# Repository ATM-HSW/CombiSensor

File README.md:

# CombiSensor
MCU plattform + Sensor module for several environmental sensors + LoRaWAN

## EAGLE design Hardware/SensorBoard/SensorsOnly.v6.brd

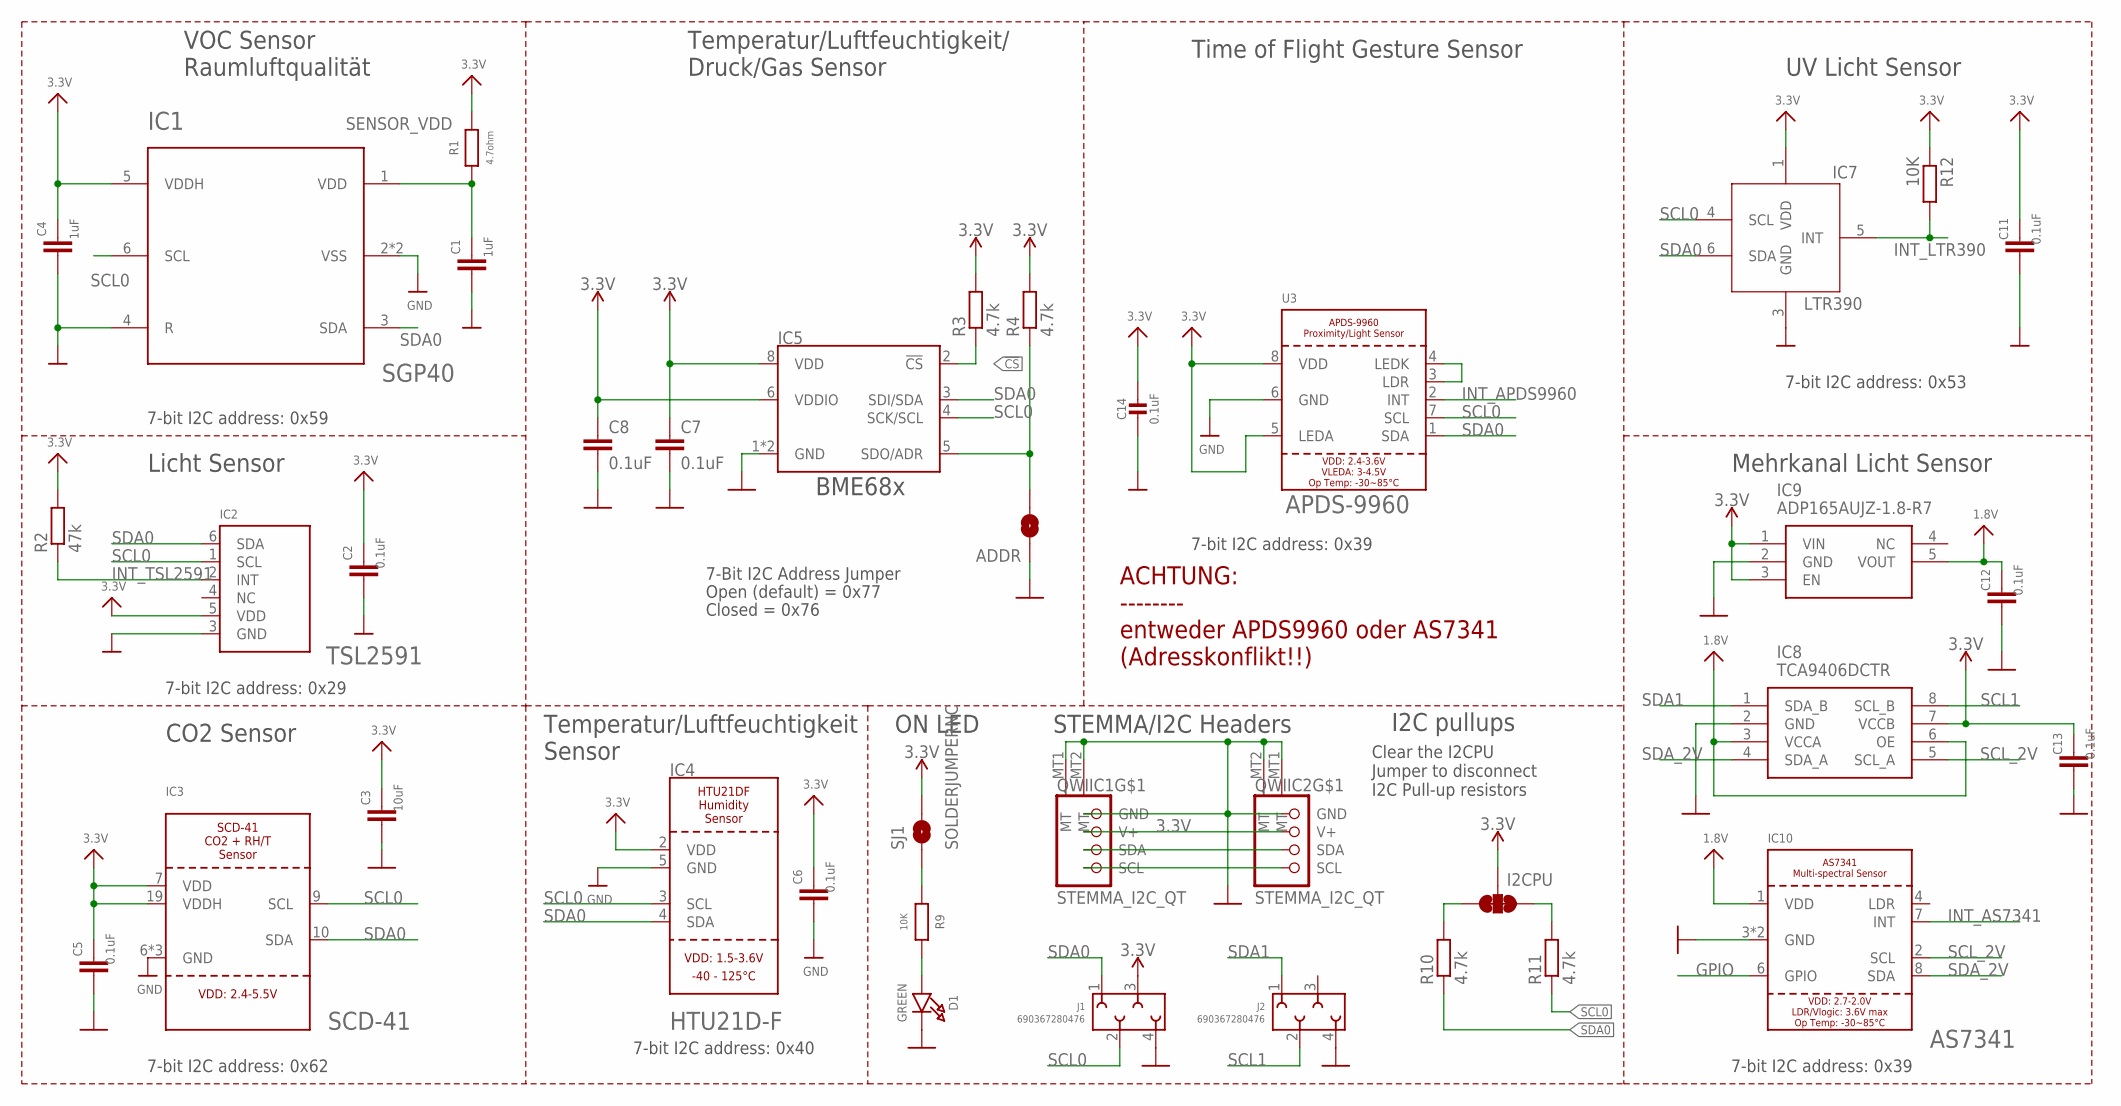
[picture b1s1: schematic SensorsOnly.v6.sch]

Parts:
ADDR: JUMPER-SMT_2_NO_SILK; SMT-JUMPER_2_NO_SILK
C1, C4: 1uF; C0805
C2, C5, C6, C7, C8, C11, C12, C13: 0.1uF; C0603
C3: 10uF; C0805
C14: 0.1uF; 0603-NO
D1: GREEN; CHIPLED_0603_NOOUTLINE
I2CPU: I2C PU; SMT-JUMPER_3_2-NC_TRACE_SILK
IC1: SGP40; SGP30
IC2: TSL2591; DFN6_TAOS
IC3: SCD-41; SCD41
IC4: HTU21D-F; HTU21DF
IC5: BME680 Air Quality Sensor; LGA3.0X3.0
IC7: LTR390
IC8: TCA9406DCTR; SOP65P400X130-8N
IC9: ADP165AUJZ-1.8-R7; SOT95P280X100-5N
IC10: AS7341
J1, J2: 690367280476
QWIIC1, QWIIC2: STEMMA_I2C_QT; JST_SH4
R1: 4.7ohm; R0603
R2: 47k; R0603
R3, R4, R10, R11: 4.7k; R0603
R9, R12: 10K; R0603
SJ1: SOLDERJUMPERNC; SJ_2S
U3: APDS-9960

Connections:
1.8V: C12.1, IC8.3 (VCCA), IC8.6 (OE), IC9.5 (VOUT), IC10.1 (VDD)
3.3V: C2.1, C3.1, C4.1, C5.1, C6.1, C7.1, C8.1, C11.1, C13.1, C14.1, I2CPU.2, IC1.5 (VDDH), IC2.5 (VDD), IC3.7 (VDD), IC3.19 (VDDH), IC4.2 (VDD), IC5.6 (VDDIO), IC5.8 (VDD), IC7.1 (VDD), IC8.7 (VCCB), IC9.1 (VIN), IC9.3 (EN), J1.3, QWIIC1.2 (V+), QWIIC2.2 (V+), R1.2, R2.2, R3.2, R4.2, R12.1, SJ1.2, U3.5 (LEDA), U3.8 (VDD)
!CS: IC5.2 (!CS), R3.1
GND: ADDR.1, C1.2, C2.2, C3.2, C4.2, C5.2, C6.2, C7.2, C8.2, C11.2, C12.2, C13.2, C14.2, D1.C, IC1.2 (VSS), IC1.4 (R), IC1.P$7 (VSS), IC2.3 (GND), IC3.6 (GND), IC3.20 (GND), IC3.P$1 (GND), IC4.5 (GND), IC5.1 (GND), IC5.7 (GND), IC7.3 (GND), IC8.2 (GND), IC9.2 (GND), IC10.3 (GND), IC10.5 (GND), J1.4, J2.4, QWIIC1.1 (GND), QWIIC1.MT1 (MT), QWIIC1.MT2 (MT), QWIIC2.1 (GND), QWIIC2.MT1 (MT), QWIIC2.MT2 (MT), U3.6 (GND)
GPIO: IC10.6 (GPIO)
INT_APDS9960: U3.2 (INT)
INT_AS7341: IC10.7 (INT)
INT_LTR390: IC7.5 (INT), R12.2
INT_TSL2591: IC2.2 (INT), R2.1
unnamed: D1.A, R9.2
unnamed: U3.3 (LDR), U3.4 (LEDK)
unnamed: R9.1, SJ1.1
unnamed: I2CPU.3, R10.2
unnamed: I2CPU.1, R11.2
SCL0: IC1.6 (SCL), IC2.1 (SCL), IC3.9 (SCL), IC4.3 (SCL), IC5.4 (SCK/SCL), IC7.4 (SCL), J1.2, QWIIC1.4 (SCL), QWIIC2.4 (SCL), R11.1, U3.7 (SCL)
SCL1: IC8.8 (SCL_B), J2.2
SCL_2V: IC8.5 (SCL_A), IC10.2 (SCL)
SDA0: IC1.3 (SDA), IC2.6 (SDA), IC3.10 (SDA), IC4.4 (SDA), IC5.3 (SDI/SDA), IC7.6 (SDA), J1.1, QWIIC1.3 (SDA), QWIIC2.3 (SDA), R10.1, U3.1 (SDA)
SDA1: IC8.1 (SDA_B), J2.1
SDA_2V: IC8.4 (SDA_A), IC10.8 (SDA)
SDO/ADR: ADDR.2, IC5.5 (SDO/ADR), R4.1
SENSOR_VDD: C1.1, IC1.1 (VDD), R1.1

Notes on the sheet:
STEMMA/I2C Headers
ON LED
7-Bit I2C Address Jumper
Open (default) = 0x77
Closed = 0x76
Clear the I2CPU Jumper to disconnect I2C Pull-up resistors
7-bit I2C address: 0x39
Time of Flight Gesture Sensor
I2C pullups
7-bit I2C address: 0x40
7-bit I2C address: 0x62
7-bit I2C address: 0x29
7-bit I2C address: 0x59
7-bit I2C address: 0x53
ACHTUNG: -------- entweder APDS9960 oder AS7341 (Adresskonflikt!!)
VOC Sensor Raumluftqualität
Temperatur/Luftfeuchtigkeit/ Druck/Gas Sensor
UV Licht Sensor
Mehrkanal Licht Sensor
Temperatur/Luftfeuchtigkeit Sensor
CO2 Sensor
Licht Sensor
BME68x

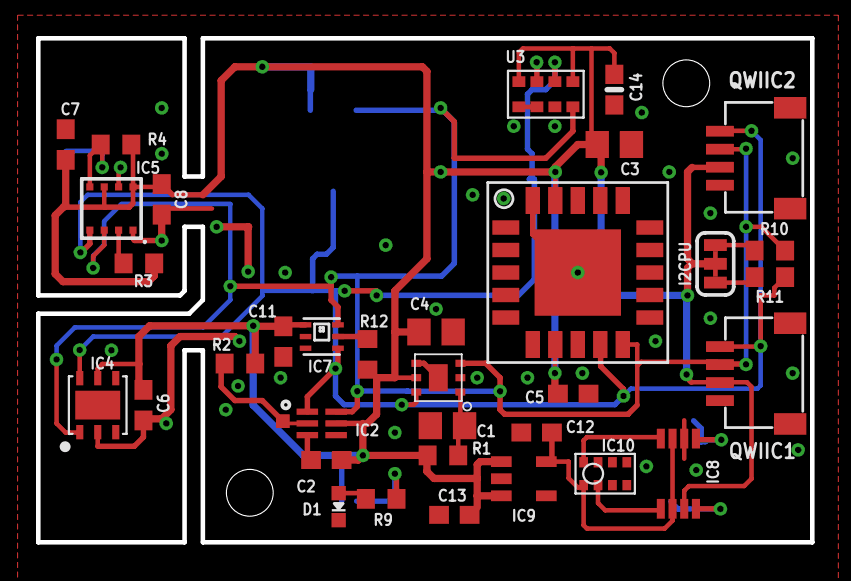
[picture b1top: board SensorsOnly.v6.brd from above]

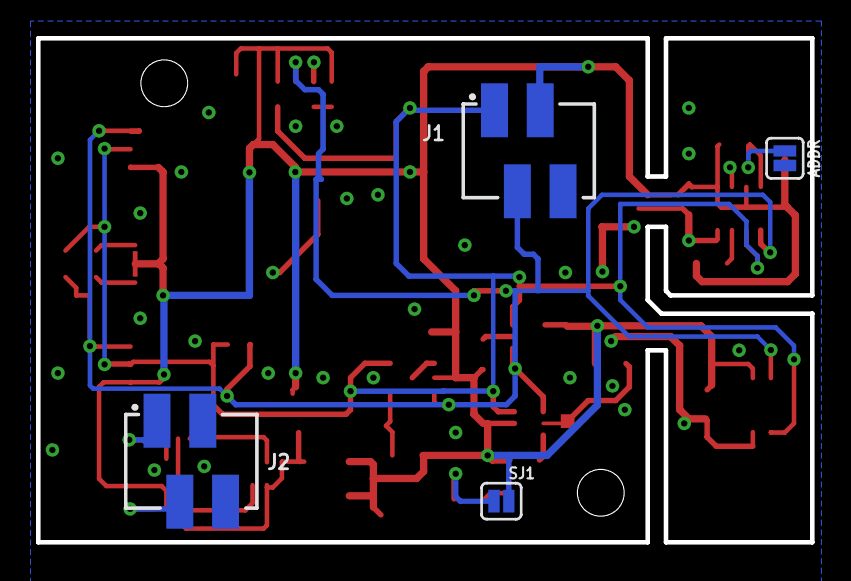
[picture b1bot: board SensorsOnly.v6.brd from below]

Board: 2 copper layers, 43.0 x 28.0 mm, 38 parts (4 on the bottom side), 19 nets.

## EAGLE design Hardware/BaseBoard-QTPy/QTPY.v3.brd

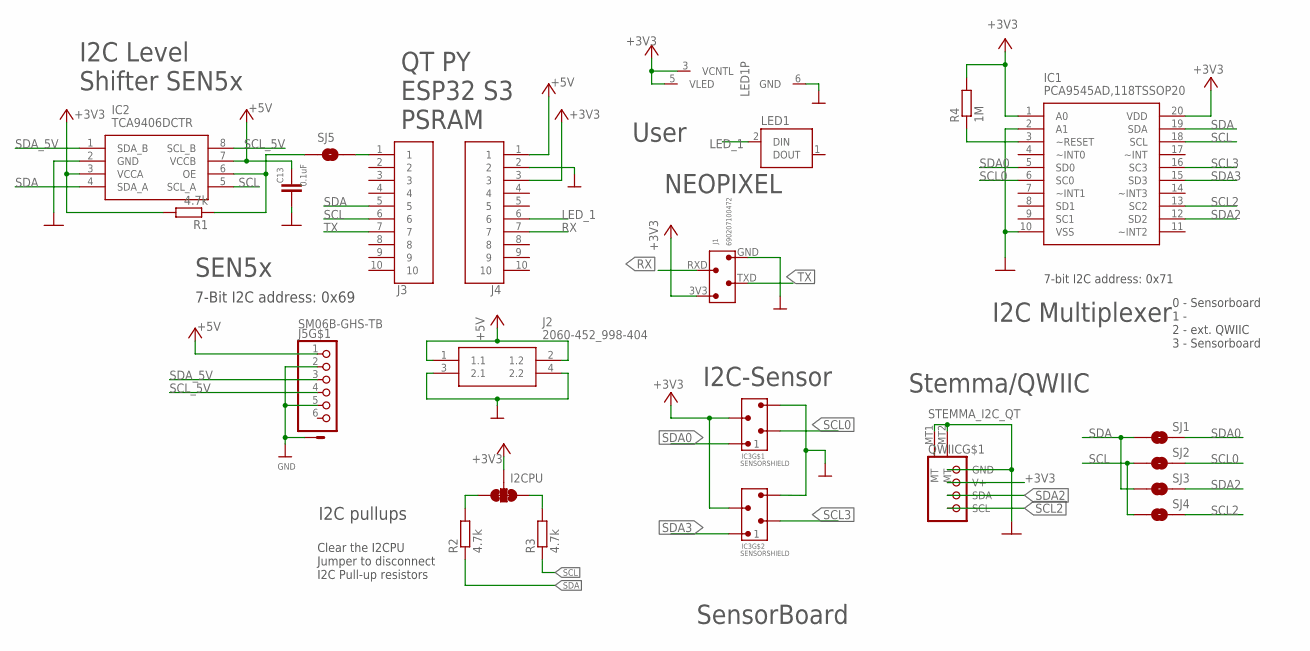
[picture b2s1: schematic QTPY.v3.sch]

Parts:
C13: 0.1uF; C0603
I2CPU: I2C PU; SMT-JUMPER_3_2-NC_TRACE_SILK
IC1: PCA9545AD,118TSSOP20; TSSOP20
IC2: TCA9406DCTR; SOP65P400X130-8N
IC3: SENSORSHIELD
J1: 690207100472; LORASHIELD
J2: 2060-452_998-404; 2060452998404
J3, J4: BG125-10-A-1-1-0440-N-D; BG12510A110440ND
J5: SM06B-GHS-TB; JST-PH-06-SMD
LED1: WS2812WS2812; WS2812
QWIIC: STEMMA_I2C_QT; JST_SH4
R1, R2, R3: 4.7k; R0603
R4: 1M; R0603
SJ1, SJ2, SJ3, SJ4, SJ5: SOLDERJUMPERNO; SJ_2S-NO

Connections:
+3V3: I2CPU.2, IC1.1 (A0), IC1.20 (VDD), IC2.3 (VCCA), IC3.3V3_1 (3), IC3.3V3_2 (3), J1.3V3 (4), J3.3, LED1.3 (VCNTL), LED1.5 (VLED), QWIIC.2 (V+), R1.2, R4.2
+5V: C13.1, IC2.7 (VCCB), J2.1 (1.1), J2.2 (1.2), J3.1, J5.1
GND: C13.2, IC1.2 (A1), IC1.10 (VSS), IC2.2 (GND), IC3.GND_1 (4), IC3.GND_2 (4), J1.GND (1), J2.3 (2.1), J2.4 (2.2), J3.2, J5.2, J5.5, J5.7 (S), J5.8 (S), LED1.6 (GND), QWIIC.1 (GND), QWIIC.MT1 (MT), QWIIC.MT2 (MT)
LED_1: J3.6, LED1.2 (DIN)
unnamed: IC2.6 (OE), R1.1, SJ5.1
unnamed: J4.1, SJ5.2
unnamed: IC1.3 (~RESET), R4.1
unnamed: I2CPU.3, R2.2
unnamed: I2CPU.1, R3.2
RX: J1.RXD (2), J3.7
SCL: IC1.18 (SCL), IC2.5 (SCL_A), J4.6, R3.1, SJ2.1, SJ4.1
SCL0: IC1.6 (SC0), IC3.SCL0 (2), SJ2.2
SCL2: IC1.13 (SC2), QWIIC.4 (SCL), SJ4.2
SCL3: IC1.16 (SC3), IC3.SCL1 (2)
SCL_5V: IC2.8 (SCL_B), J5.4
SDA: IC1.19 (SDA), IC2.4 (SDA_A), J4.5, R2.1, SJ1.1, SJ3.1
SDA0: IC1.5 (SD0), IC3.SDA0 (1), SJ1.2
SDA2: IC1.12 (SD2), QWIIC.3 (SDA), SJ3.2
SDA3: IC1.15 (SD3), IC3.SDA1 (1)
SDA_5V: IC2.1 (SDA_B), J5.3
TX: J1.TXD (3), J4.7

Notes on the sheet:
SensorBoard
User
Stemma/QWIIC
QT PY ESP32 S3 PSRAM
7-bit I2C address: 0x71
I2C Multiplexer
0 - Sensorboard 1 - 2 - ext. QWIIC 3 - Sensorboard
NEOPIXEL
Clear the I2CPU Jumper to disconnect I2C Pull-up resistors
I2C pullups
I2C-Sensor
I2C Level Shifter SEN5x
SEN5x
7-Bit I2C address: 0x69

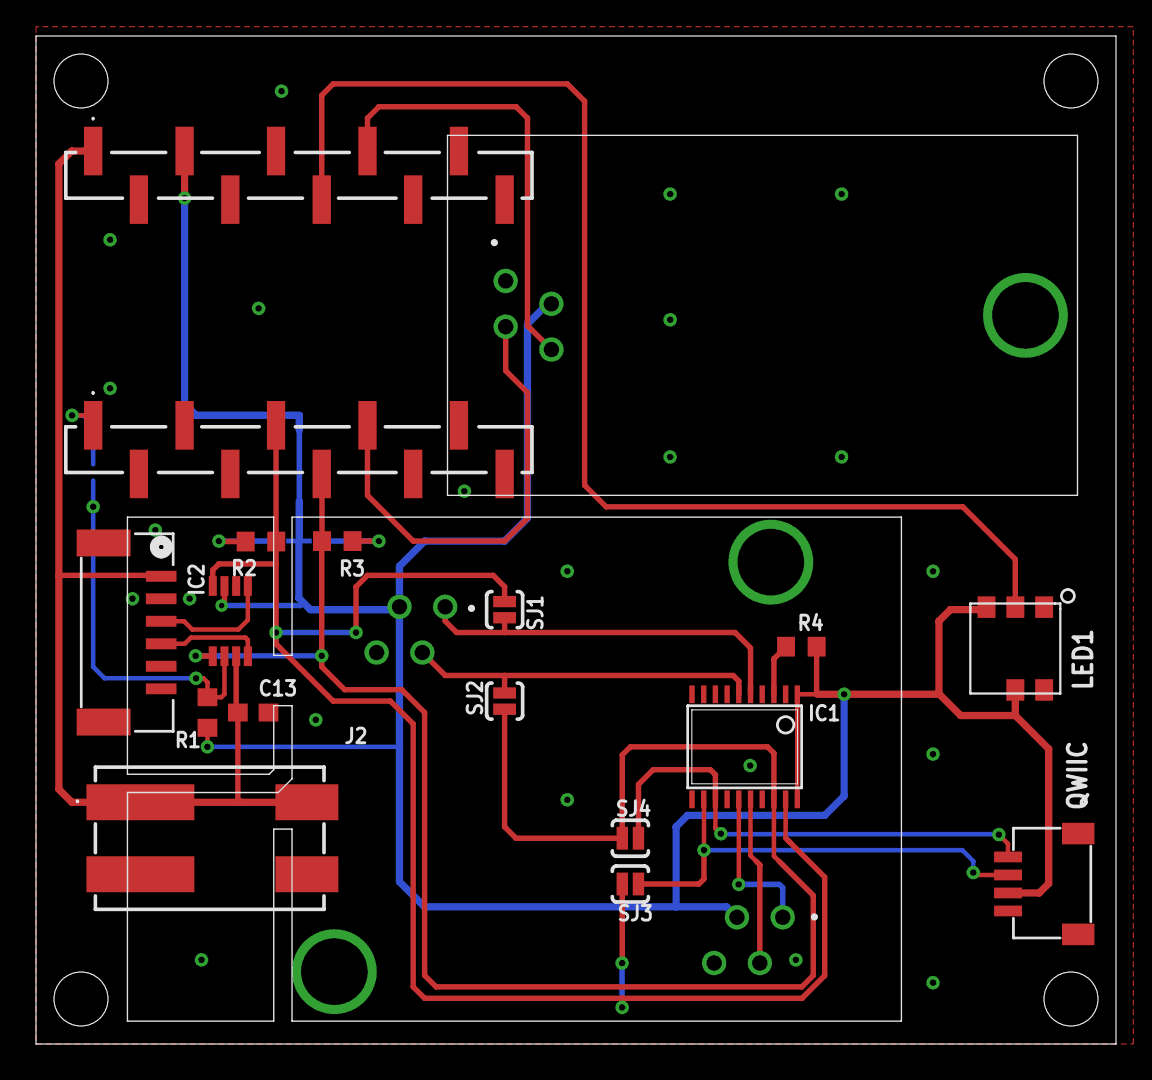
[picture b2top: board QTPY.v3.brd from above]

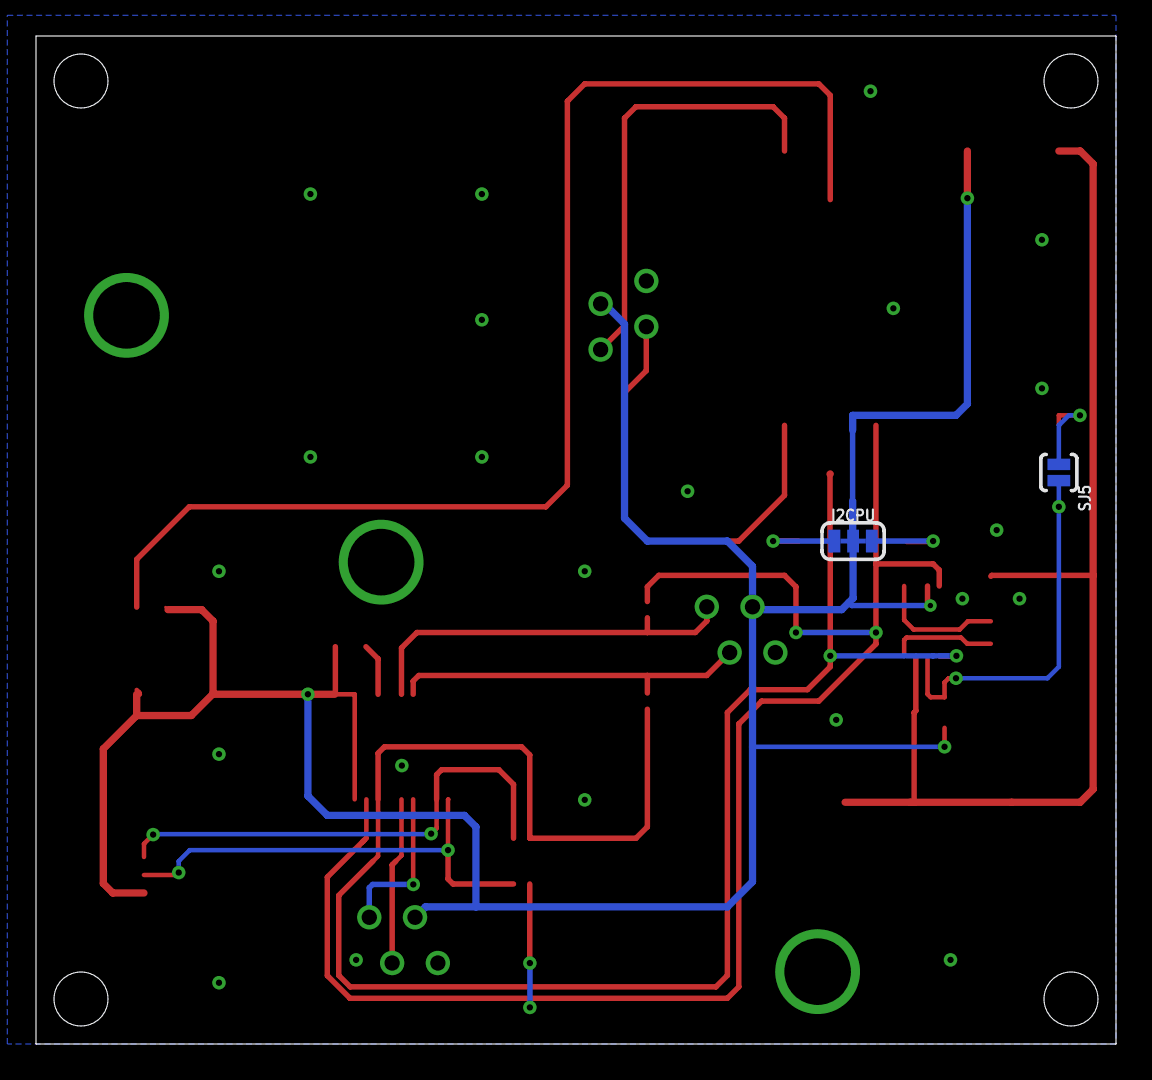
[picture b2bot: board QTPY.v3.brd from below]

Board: 2 copper layers, 60.0 x 56.0 mm, 21 parts (2 on the bottom side), 21 nets.

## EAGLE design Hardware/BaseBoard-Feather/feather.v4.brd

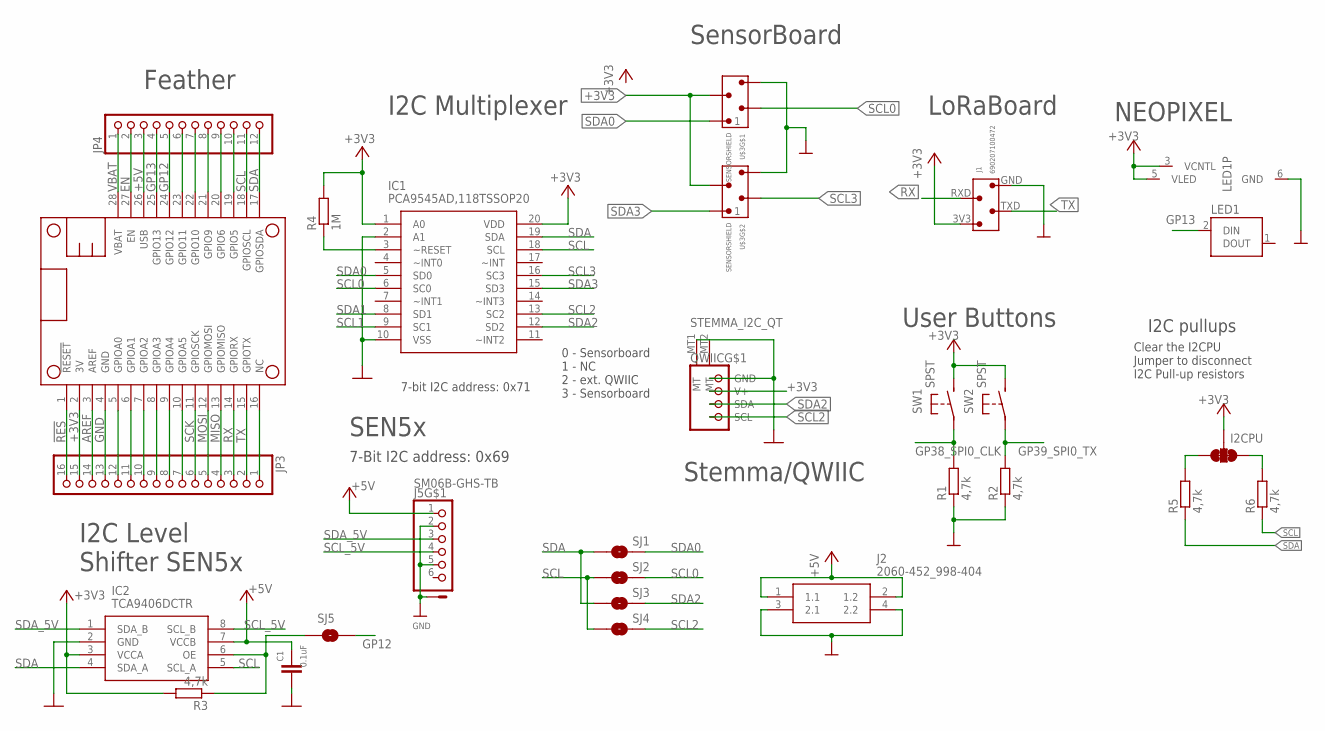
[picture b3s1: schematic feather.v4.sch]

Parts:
C1: 0.1uF; C0603
I2CPU: I2C PU; SMT-JUMPER_3_2-NC_TRACE_SILK
IC1: PCA9545AD,118TSSOP20; TSSOP20
IC2: TCA9406DCTR; SOP65P400X130-8N
J1: 690207100472; LORASHIELD
J2: 2060-452_998-404; 2060452998404
J5: SM06B-GHS-TB; JST-PH-06-SMD
JP3: HEADER-1X16_76MIL; 1X16_ROUND_76MIL
JP4: HEADER-1X1276MIL; 1X12_ROUND_76MIL
LED1: WS2812WS2812; WS2812
MS1: FEATHERWING_NODIM; FEATHERWING_DIM
QWIIC: STEMMA_I2C_QT; JST_SH4
R1, R2, R3, R5, R6: 4,7k; R0603
R4: 1M; R0603
SJ1, SJ2, SJ3, SJ4, SJ5: SOLDERJUMPERNO; SJ_2S-NO
SW1, SW2: SPST; DTSM-32S-B
U$3: SENSORSHIELD

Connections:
!RES: JP3.16, MS1.1 (!RESET)
+3V3: I2CPU.2, IC1.1 (A0), IC1.20 (VDD), IC2.3 (VCCA), J1.3V3 (4), JP3.15, LED1.3 (VCNTL), LED1.5 (VLED), MS1.2 (3V), QWIIC.2 (V+), R3.2, R4.2, SW1.P$2 (S), SW2.P$2 (S), U$3.3V3_1 (3), U$3.3V3_2 (3)
+5V: C1.1, IC2.7 (VCCB), J2.1 (1.1), J2.2 (1.2), J5.1, JP4.3, MS1.26 (USB)
AREF: JP3.14, MS1.3 (AREF)
EN: JP4.2, MS1.27 (EN)
GND: C1.2, IC1.2 (A1), IC1.10 (VSS), IC2.2 (GND), J1.GND (1), J2.3 (2.1), J2.4 (2.2), J5.2, J5.5, J5.7 (S), J5.8 (S), JP3.12, JP3.13, LED1.6 (GND), MS1.4 (GND), MS1.5 (GPIOA0), QWIIC.1 (GND), QWIIC.MT1 (MT), QWIIC.MT2 (MT), R1.1, R2.1, U$3.GND_1 (4), U$3.GND_2 (4)
GP12: JP4.5, MS1.24 (GPIO12), SJ5.2
GP13: JP4.4, LED1.2 (DIN), MS1.25 (GPIO13)
GP38_SPI0_CLK: R1.2, SW1.P$1
GP39_SPI0_TX: R2.2, SW2.P$1
MISO: JP3.4, MS1.13 (GPIOMISO)
MOSI: JP3.5, MS1.12 (GPIOMOSI)
unnamed: IC2.6 (OE), R3.1, SJ5.1
unnamed: JP3.1, MS1.16 (NC)
unnamed: IC1.3 (~RESET), R4.1
unnamed: I2CPU.3, R5.2
unnamed: I2CPU.1, R6.2
unnamed: JP3.7, MS1.10 (GPIOA5)
unnamed: JP3.8, MS1.9 (GPIOA4)
unnamed: JP3.9, MS1.8 (GPIOA3)
unnamed: JP3.10, MS1.7 (GPIOA2)
unnamed: JP3.11, MS1.6 (GPIOA1)
unnamed: JP4.6, MS1.23 (GPIO11)
unnamed: JP4.7, MS1.22 (GPIO10)
unnamed: JP4.8, MS1.21 (GPIO9)
unnamed: JP4.9, MS1.20 (GPIO6)
unnamed: JP4.10, MS1.19 (GPIO5)
RX: J1.RXD (2), JP3.3, MS1.14 (GPIORX)
SCK: JP3.6, MS1.11 (GPIOSCK)
SCL: IC1.18 (SCL), IC2.5 (SCL_A), JP4.11, MS1.18 (GPIOSCL), R6.1, SJ2.1, SJ4.1
SCL0: IC1.6 (SC0), SJ2.2, U$3.SCL0 (2)
SCL1: IC1.9 (SC1)
SCL2: IC1.13 (SC2), QWIIC.4 (SCL), SJ4.2
SCL3: IC1.16 (SC3), U$3.SCL1 (2)
SCL_5V: IC2.8 (SCL_B), J5.4
SDA: IC1.19 (SDA), IC2.4 (SDA_A), JP4.12, MS1.17 (GPIOSDA), R5.1, SJ1.1, SJ3.1
SDA0: IC1.5 (SD0), SJ1.2, U$3.SDA0 (1)
SDA1: IC1.8 (SD1)
SDA2: IC1.12 (SD2), QWIIC.3 (SDA), SJ3.2
SDA3: IC1.15 (SD3), U$3.SDA1 (1)
SDA_5V: IC2.1 (SDA_B), J5.3
TX: J1.TXD (3), JP3.2, MS1.15 (GPIOTX)
VBAT: JP4.1, MS1.28 (VBAT)

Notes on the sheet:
SensorBoard
User Buttons
Stemma/QWIIC
Feather
7-bit I2C address: 0x71
I2C Multiplexer
0 - Sensorboard 1 - NC 2 - ext. QWIIC 3 - Sensorboard
NEOPIXEL
Clear the I2CPU Jumper to disconnect I2C Pull-up resistors
I2C pullups
LoRaBoard
SEN5x
I2C Level Shifter SEN5x
7-Bit I2C address: 0x69

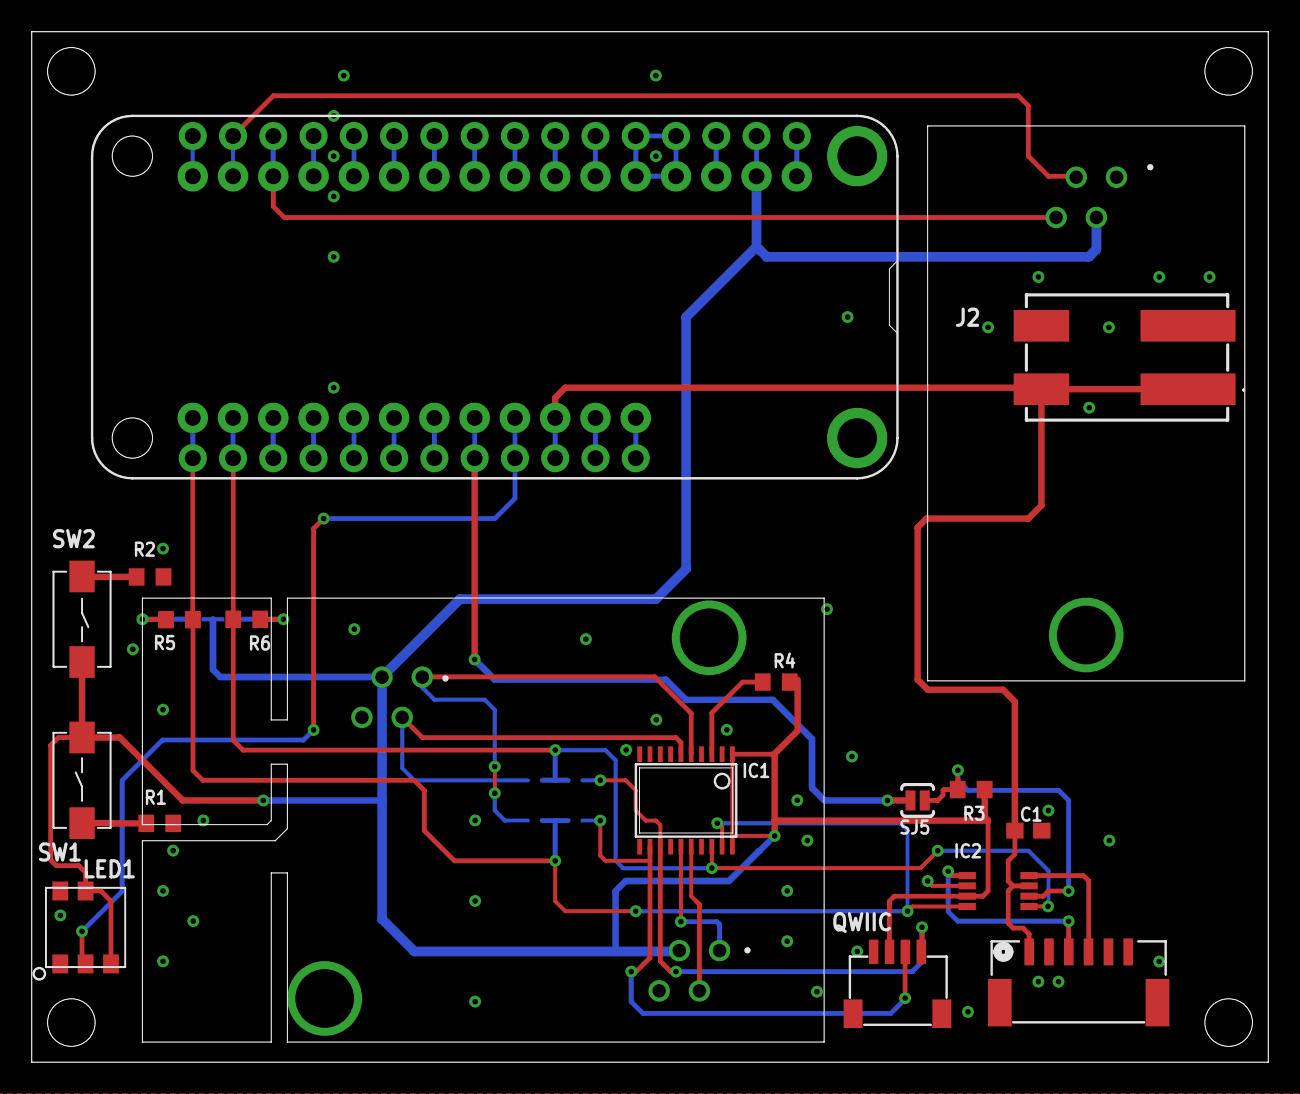
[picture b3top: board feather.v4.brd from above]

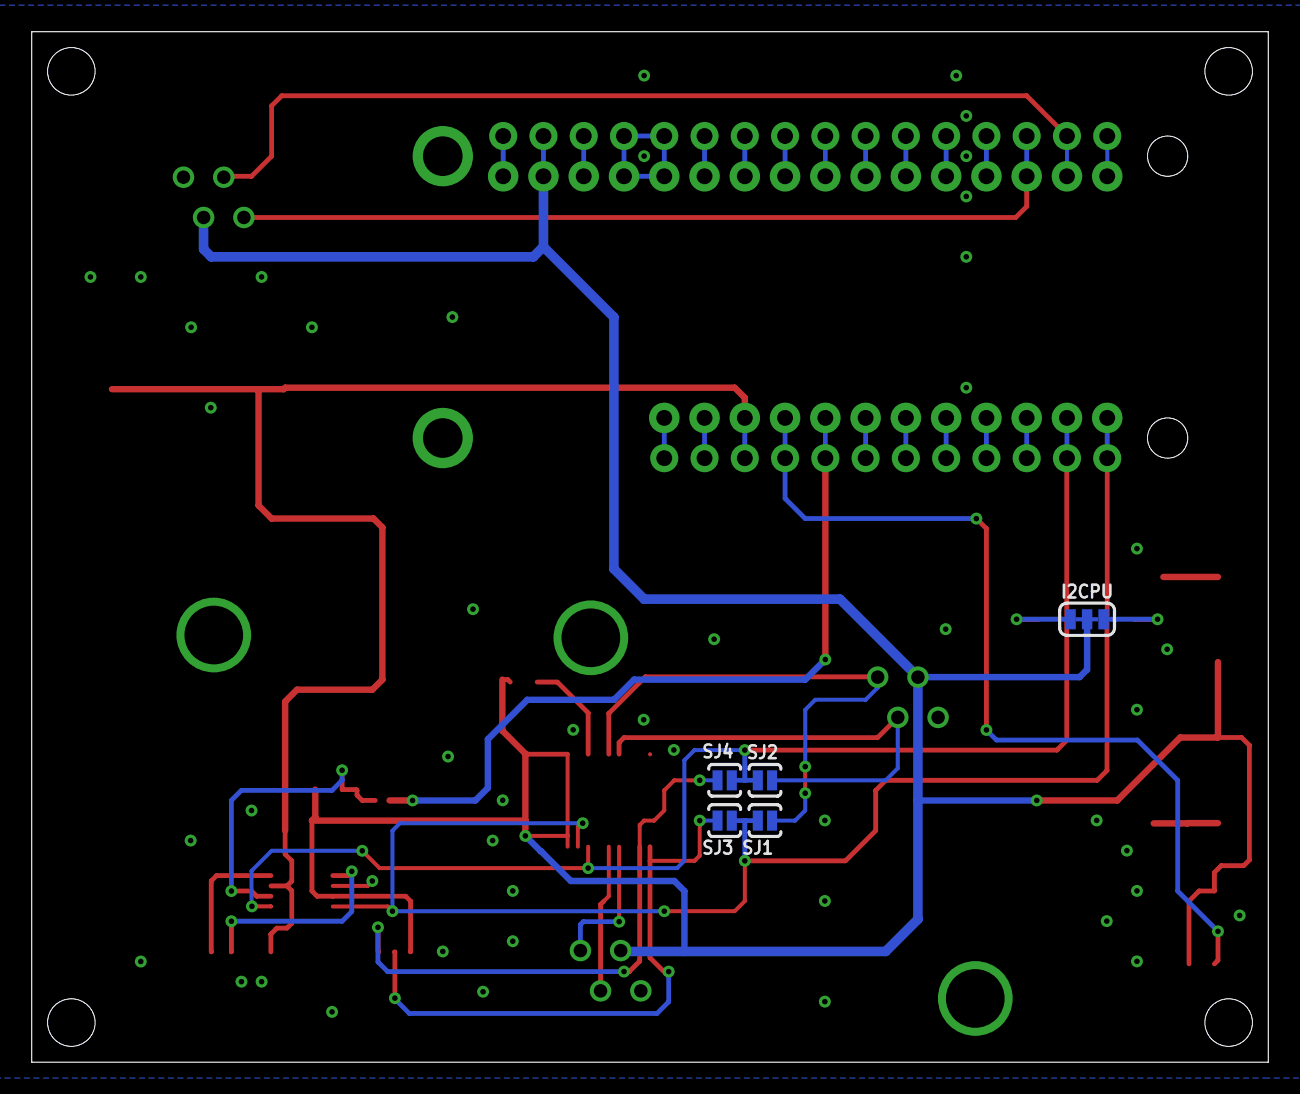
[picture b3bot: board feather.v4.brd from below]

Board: 2 copper layers, 78.0 x 65.0 mm, 26 parts (5 on the bottom side), 41 nets.

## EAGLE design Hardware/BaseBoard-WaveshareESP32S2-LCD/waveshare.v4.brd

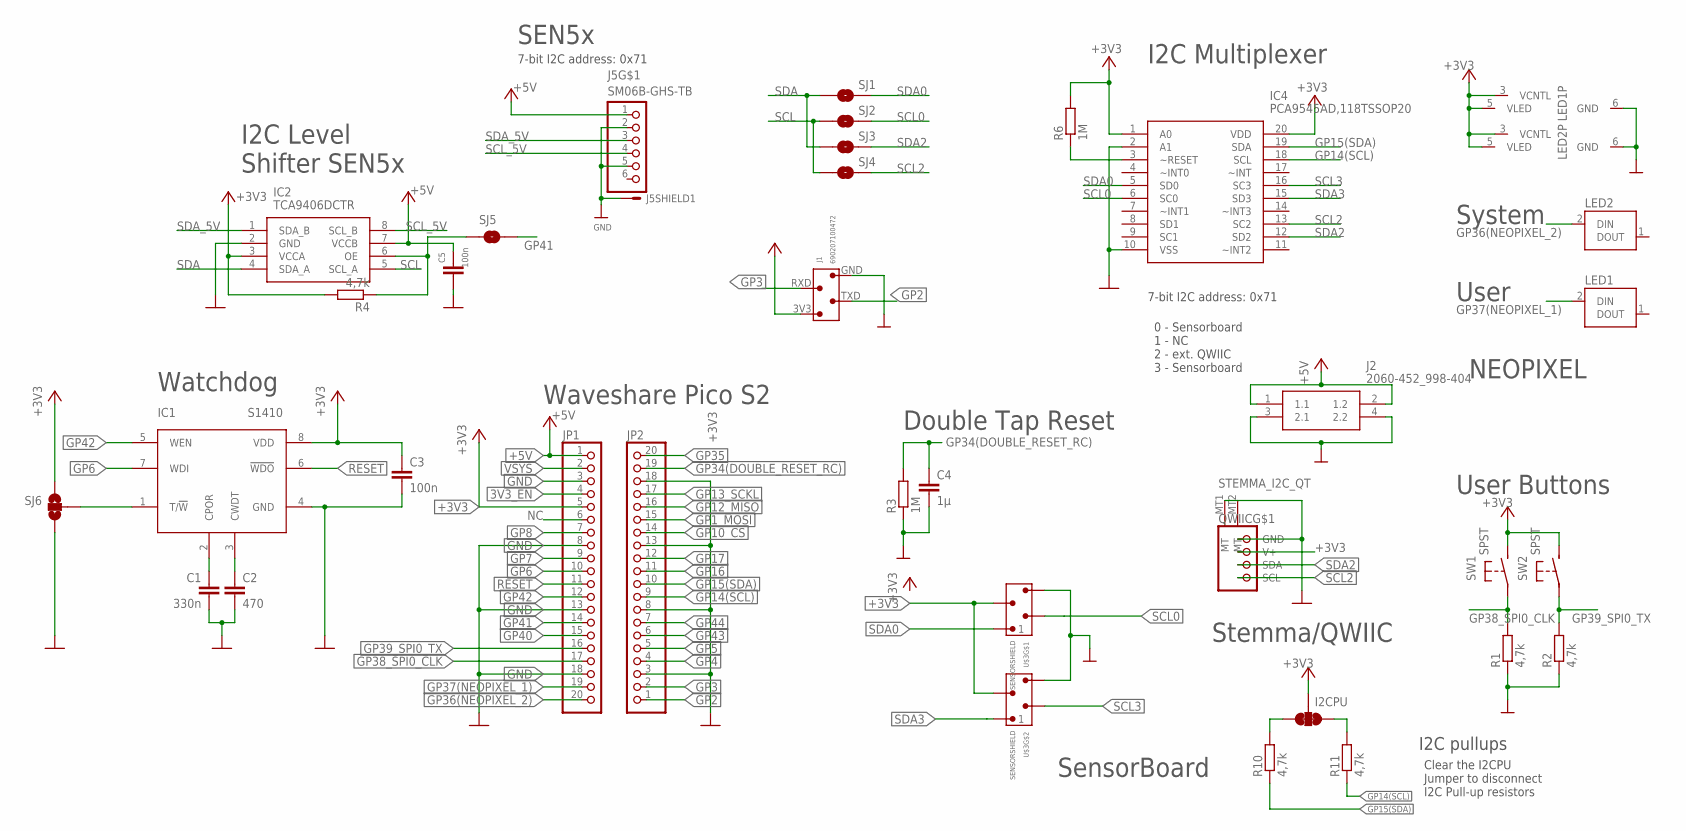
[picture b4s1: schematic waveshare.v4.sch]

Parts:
C1: 330n; C0603
C2: 470; C0603
C3, C5: 100n; C0603
C4: 1µ; C0603
I2CPU: I2C PU; SMT-JUMPER_3_2-NC_TRACE_SILK
IC1: S1410; MSOP08
IC2: TCA9406DCTR; SOP65P400X130-8N
IC4: PCA9545AD,118TSSOP20; TSSOP20
J1: 690207100472; LORASHIELD
J2: 2060-452_998-404; 2060452998404
J5: SM06B-GHS-TB; JST-PH-06-SMD
JP1, JP2: PINHD-1X20; 1X20
LED1, LED2: WS2812WS2812; WS2812
QWIIC: STEMMA_I2C_QT; JST_SH4
R1, R2, R4, R10, R11: 4,7k; R0603
R3, R6: 1M; R0603
SJ1, SJ2, SJ3, SJ4, SJ5: SOLDERJUMPERNO; SJ_2S-NO
SJ6: SOLDERJUMPER_2WAYTRACE1&2; SJ_3_TRACE1&2
SW1, SW2: SPST; DTSM-32S-B
U$3: SENSORSHIELD

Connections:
3V3_EN: JP1.4
+3V3: C3.1, I2CPU.2, IC1.8 (VDD), IC2.3 (VCCA), IC4.1 (A0), IC4.20 (VDD), J1.3V3 (4), JP1.5, LED1.3 (VCNTL), LED1.5 (VLED), LED2.3 (VCNTL), LED2.5 (VLED), QWIIC.2 (V+), R4.2, R6.2, SJ6.1, SW1.P$2 (S), SW2.P$2 (S), U$3.3V3_1 (3), U$3.3V3_2 (3)
+5V: C5.1, IC2.7 (VCCB), J2.1 (1.1), J2.2 (1.2), J5.1, JP1.1
GND: C1.2, C2.2, C3.2, C4.2, C5.2, IC1.4 (GND), IC2.2 (GND), IC4.2 (A1), IC4.10 (VSS), J1.GND (1), J2.3 (2.1), J2.4 (2.2), J5.2, J5.5, J5.7 (S), J5.8 (S), JP1.3, JP1.8, JP1.13, JP1.18, JP2.3, JP2.8, JP2.13, JP2.18, LED1.6 (GND), LED2.6 (GND), QWIIC.1 (GND), QWIIC.MT1 (MT), QWIIC.MT2 (MT), R1.1, R2.1, R3.1, SJ6.3, U$3.GND_1 (4), U$3.GND_2 (4)
GP1_MOSI: JP2.15
GP2: J1.TXD (3), JP2.1
GP3: J1.RXD (2), JP2.2
GP4: JP2.4
GP5: JP2.5
GP6: IC1.7 (WDI), JP1.10
GP7: JP1.9
GP8: JP1.7
GP10_CS: JP2.14
GP12_MISO: JP2.16
GP13_SCKL: JP2.17
GP14(SCL): IC4.18 (SCL), JP2.9, R11.1
GP15(SDA): IC4.19 (SDA), JP2.10, R10.1
GP16: JP2.11
GP17: JP2.12
GP34(DOUBLE_RESET_RC): C4.1, JP2.19, R3.2
GP35: JP2.20
GP36(NEOPIXEL_2): JP1.20, LED2.2 (DIN)
GP37(NEOPIXEL_1): JP1.19, LED1.2 (DIN)
GP38_SPI0_CLK: JP1.17, R1.2, SW1.P$1
GP39_SPI0_TX: JP1.16, R2.2, SW2.P$1
GP40: JP1.15
GP41: JP1.14, SJ5.2
GP42: IC1.5 (WEN), JP1.12
GP43: JP2.6
GP44: JP2.7
unnamed: IC2.6 (OE), R4.1, SJ5.1
unnamed: C1.1, IC1.2 (CPOR)
unnamed: C2.1, IC1.3 (CWDT)
unnamed: IC1.1 (T/!W), SJ6.2
unnamed: IC4.3 (~RESET), R6.1
unnamed: I2CPU.3, R10.2
unnamed: I2CPU.1, R11.2
NC: JP1.6
RESET: IC1.6 (!WDO), JP1.11
SCL: IC2.5 (SCL_A), SJ2.1, SJ4.1
SCL0: IC4.6 (SC0), SJ2.2, U$3.SCL0 (2)
SCL2: IC4.13 (SC2), QWIIC.4 (SCL), SJ4.2
SCL3: IC4.16 (SC3), U$3.SCL1 (2)
SCL_5V: IC2.8 (SCL_B), J5.4
SDA: IC2.4 (SDA_A), SJ1.1, SJ3.1
SDA0: IC4.5 (SD0), SJ1.2, U$3.SDA0 (1)
SDA2: IC4.12 (SD2), QWIIC.3 (SDA), SJ3.2
SDA3: IC4.15 (SD3), U$3.SDA1 (1)
SDA_5V: IC2.1 (SDA_B), J5.3
VSYS: JP1.2

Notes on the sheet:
SensorBoard
User
System
Double Tap Reset
User Buttons
Stemma/QWIIC
Watchdog
Waveshare Pico S2
7-bit I2C address: 0x71
I2C Multiplexer
0 - Sensorboard 1 - NC 2 - ext. QWIIC 3 - Sensorboard
NEOPIXEL
Clear the I2CPU Jumper to disconnect I2C Pull-up resistors
I2C pullups
SEN5x
I2C Level Shifter SEN5x

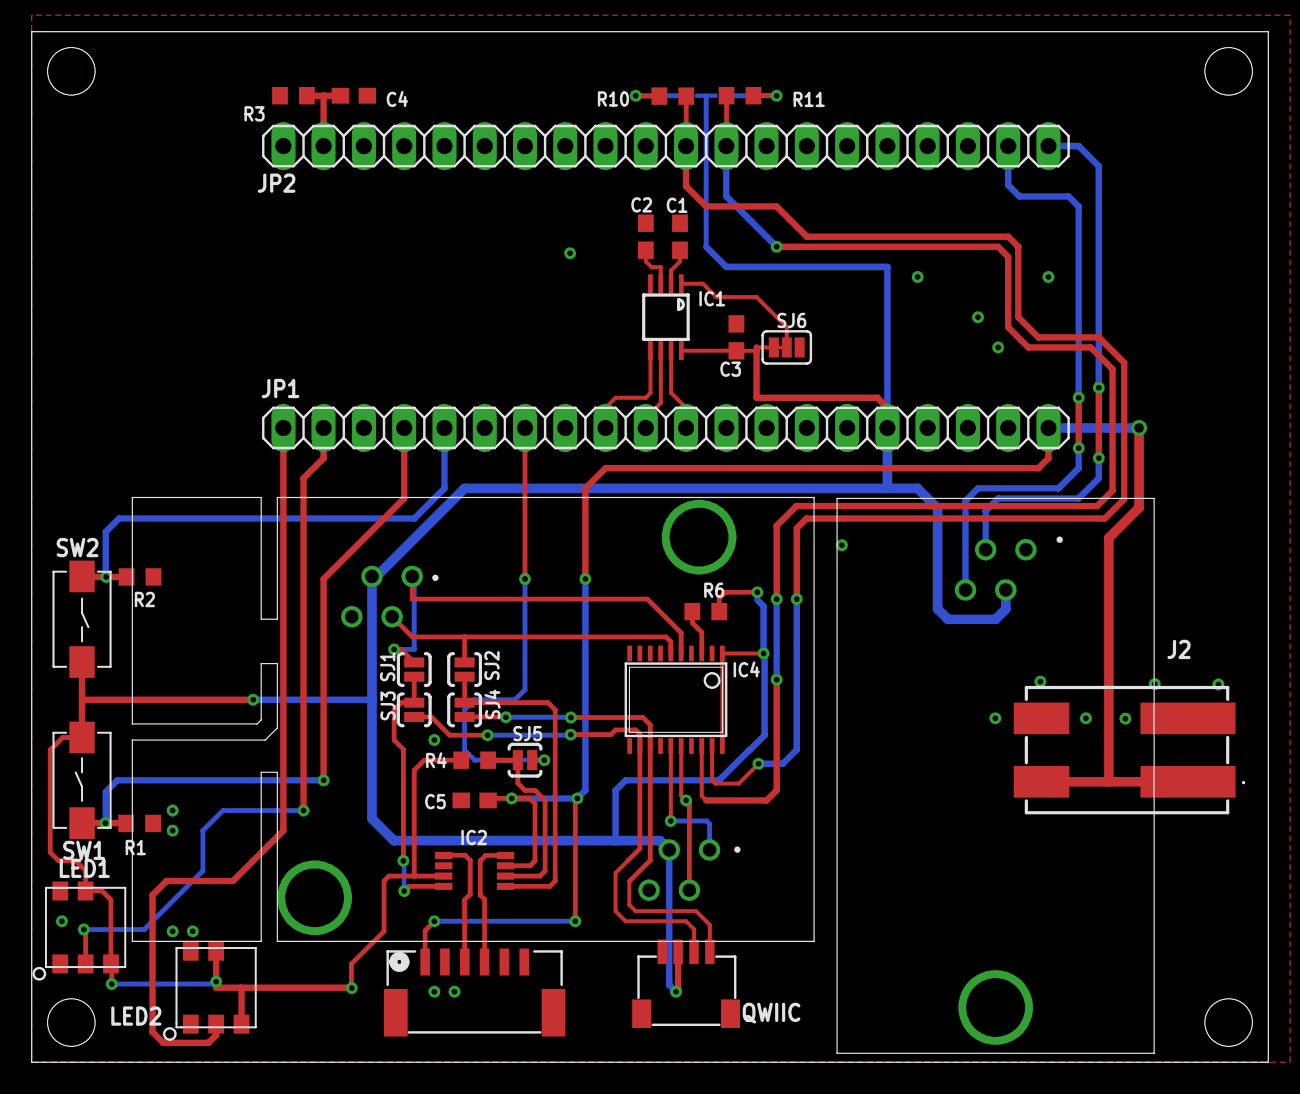
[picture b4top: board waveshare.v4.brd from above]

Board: 2 copper layers, 78.0 x 65.0 mm, 33 parts (1 on the bottom side), 33 nets.

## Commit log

2025-03-10 adding hardware and esphome integration
2025-03-10 adding circuitpython for waveshar dun qt py mcu boards
2025-05-25 SW Stand für SensorBoard+Sen5x, Sen6x und SDS011+BMP280

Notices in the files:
parts and their libraries:
microbuilder: This work is placed in the public domain, and may be freely used for commercial and non-commercial work with the following conditions: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
SparkFun-Jumpers: Licensing: Creative Commons ShareAlike 4.0 International - https://creativecommons.org/licenses/by-sa/4.0
